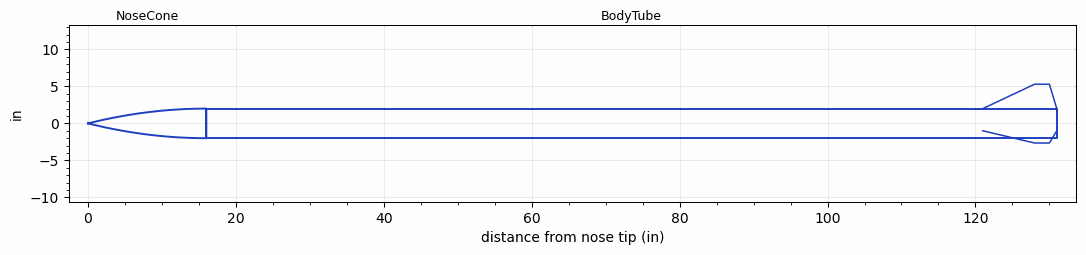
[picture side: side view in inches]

<RASAeroDocument>
 <FileVersion>2</FileVersion>
 <RocketDesign>
  <NoseCone>
   <Length>16</Length>
   <Diameter>4</Diameter>
   <Shape>Parabolic</Shape>
   <Location>0</Location>
  </NoseCone>
  <BodyTube>
   <Length>115</Length>
   <Diameter>4</Diameter>
   <Location>16</Location>
   <Fin>
    <Count>3</Count>
    <Chord>10</Chord>
    <Span>3.3</Span>
    <SweepDistance>7</SweepDistance>
    <TipChord>2</TipChord>
    <Thickness>0.25</Thickness>
    <LERadius>0.125</LERadius>
    <Location>10</Location>
    <AirfoilSection>Double Wedge</AirfoilSection>
    <FX1>1</FX1>
   </Fin>
  </BodyTube>
  <Surface>Galvanized Metal</Surface>
  <ModifiedBarrowman>False</ModifiedBarrowman>
  <Turbulence>False</Turbulence>
  <UseBooster1>False</UseBooster1>
  <UseBooster2>False</UseBooster2>
 </RocketDesign>
 <LaunchSite>
  <Altitude>5000</Altitude>
  <Pressure>0</Pressure>
  <RodAngle>7</RodAngle>
  <RodLength>18</RodLength>
  <Temperature>95</Temperature>
  <WindSpeed>45</WindSpeed>
 </LaunchSite>
 <Recovery>
  <Altitude1>1000</Altitude1>
  <Altitude2>1000</Altitude2>
  <DeviceType1>None</DeviceType1>
  <DeviceType2>None</DeviceType2>
  <Event1>False</Event1>
  <Event2>False</Event2>
  <Size1>1</Size1>
  <Size2>1</Size2>
  <EventType1>None</EventType1>
  <EventType2>None</EventType2>
  <CD1>1.33</CD1>
  <CD2>1.33</CD2>
 </Recovery>
 <SimulationList>
  <Simulation>
   <SustainerEngine>N2900-CL  (CTI)</SustainerEngine>
   <SustainerLaunchWt>69</SustainerLaunchWt>
   <SustainerNozzleDiameter>2</SustainerNozzleDiameter>
   <SustainerCG>79</SustainerCG>
   <SustainerIgnitionDelay>0</SustainerIgnitionDelay>
   <Booster1SeparationDelay>0</Booster1SeparationDelay>
   <Booster1IgnitionDelay>0</Booster1IgnitionDelay>
   <IncludeBooster1>False</IncludeBooster1>
   <Booster2Delay>0</Booster2Delay>
   <IncludeBooster2>False</IncludeBooster2>
   <TimetoApogee>41.47905</TimetoApogee>
   <MaxAltitude>29271.87</MaxAltitude>
   <MaxVelocity>1739.785</MaxVelocity>
  </Simulation>
  <Simulation>
   <SustainerEngine>N2900-CL  (CTI)</SustainerEngine>
   <SustainerLaunchWt>72</SustainerLaunchWt>
   <SustainerNozzleDiameter>2</SustainerNozzleDiameter>
   <SustainerCG>79</SustainerCG>
   <SustainerIgnitionDelay>0</SustainerIgnitionDelay>
   <Booster1SeparationDelay>0</Booster1SeparationDelay>
   <Booster1IgnitionDelay>0</Booster1IgnitionDelay>
   <IncludeBooster1>False</IncludeBooster1>
   <Booster2Delay>0</Booster2Delay>
   <IncludeBooster2>False</IncludeBooster2>
   <TimetoApogee>50.78748</TimetoApogee>
   <MaxAltitude>45001.28</MaxAltitude>
   <MaxVelocity>2196.25</MaxVelocity>
  </Simulation>
  <Simulation>
   <SustainerEngine>N2900-CL  (CTI)</SustainerEngine>
   <SustainerLaunchWt>74</SustainerLaunchWt>
   <SustainerNozzleDiameter>2</SustainerNozzleDiameter>
   <SustainerCG>79</SustainerCG>
   <SustainerIgnitionDelay>0</SustainerIgnitionDelay>
   <Booster1SeparationDelay>0</Booster1SeparationDelay>
   <Booster1IgnitionDelay>0</Booster1IgnitionDelay>
   <IncludeBooster1>False</IncludeBooster1>
   <Booster2Delay>0</Booster2Delay>
   <IncludeBooster2>False</IncludeBooster2>
   <TimetoApogee>50.78748</TimetoApogee>
   <MaxAltitude>45001.28</MaxAltitude>
   <MaxVelocity>2196.25</MaxVelocity>
  </Simulation>
 </SimulationList>
</RASAeroDocument>
